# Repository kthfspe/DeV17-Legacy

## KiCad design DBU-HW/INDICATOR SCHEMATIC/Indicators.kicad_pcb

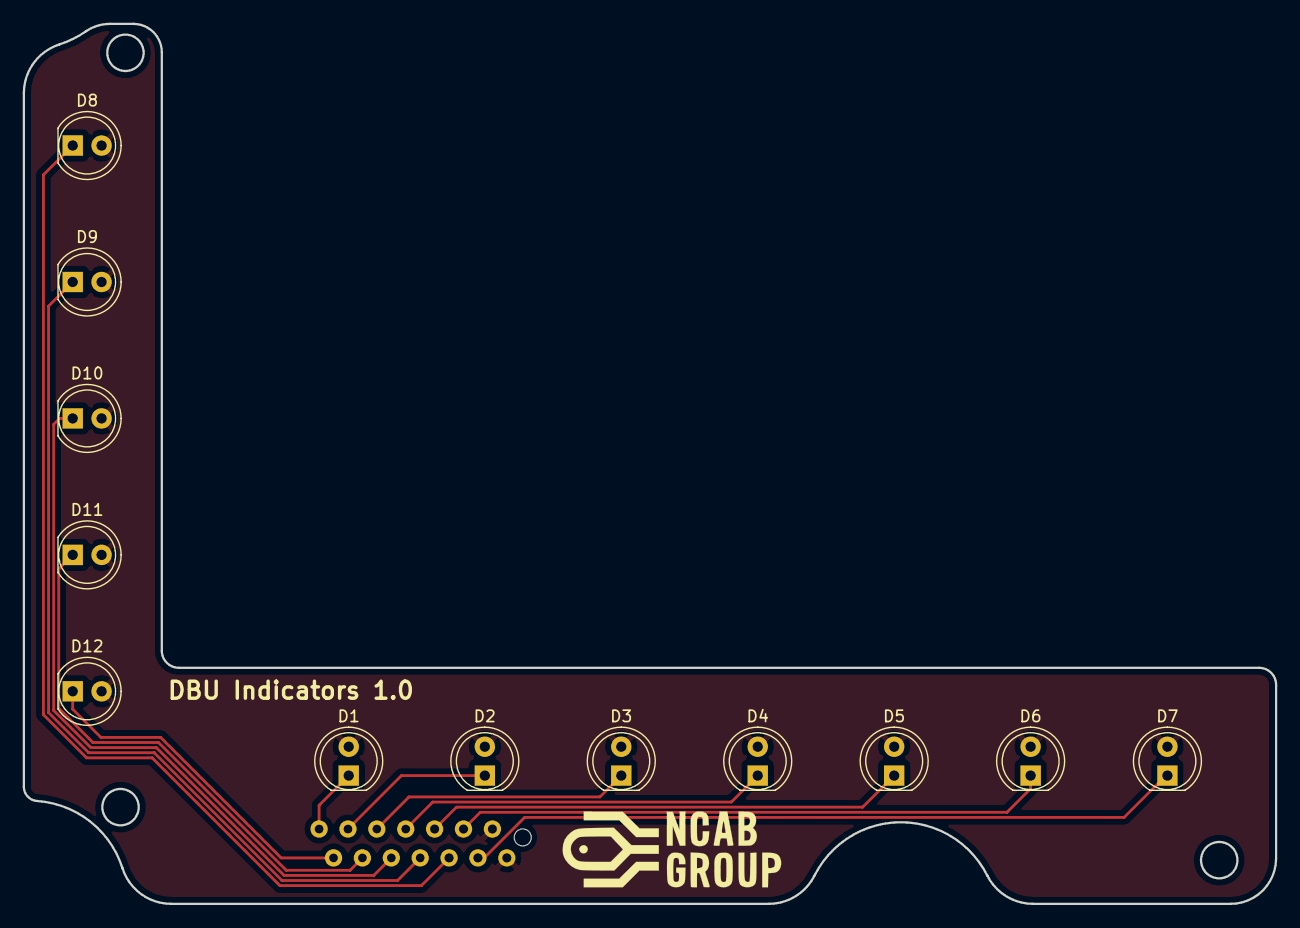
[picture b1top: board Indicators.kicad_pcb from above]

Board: 2 copper layers, 110.1 x 77.4 mm, 13 parts (1 on the bottom side), 13 nets.

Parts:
D1, D2, D3, D4, D5, D6, D7, D8, D9, D10, D11, D12: LED; LED_D5.0mm
J1: Conn_02x07_Odd_Even; Wurth-MM_female_14

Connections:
/AMI_1: D1.1, J1.14
/AMI_2: D2.1, J1.12
/AMI_3: D3.1, J1.10
/AMI_4: D4.1, J1.8
/AMI_5: D5.1, J1.6
/AMI_6: D6.1, J1.4
/AMI_7: D7.1, J1.3
/AMS_ERROR: D10.1, J1.9
/EBS_ERROR: D9.1, J1.7
/IMD_ERROR: D11.1, J1.11
/RESERVED: D12.1, J1.13
/TS_OFF: D8.1, J1.5
Vdrive: D1.2, D2.2, D3.2, D4.2, D5.2, D6.2, D7.2, D8.2, D9.2, D10.2, D11.2, D12.2, J1.1, J1.2

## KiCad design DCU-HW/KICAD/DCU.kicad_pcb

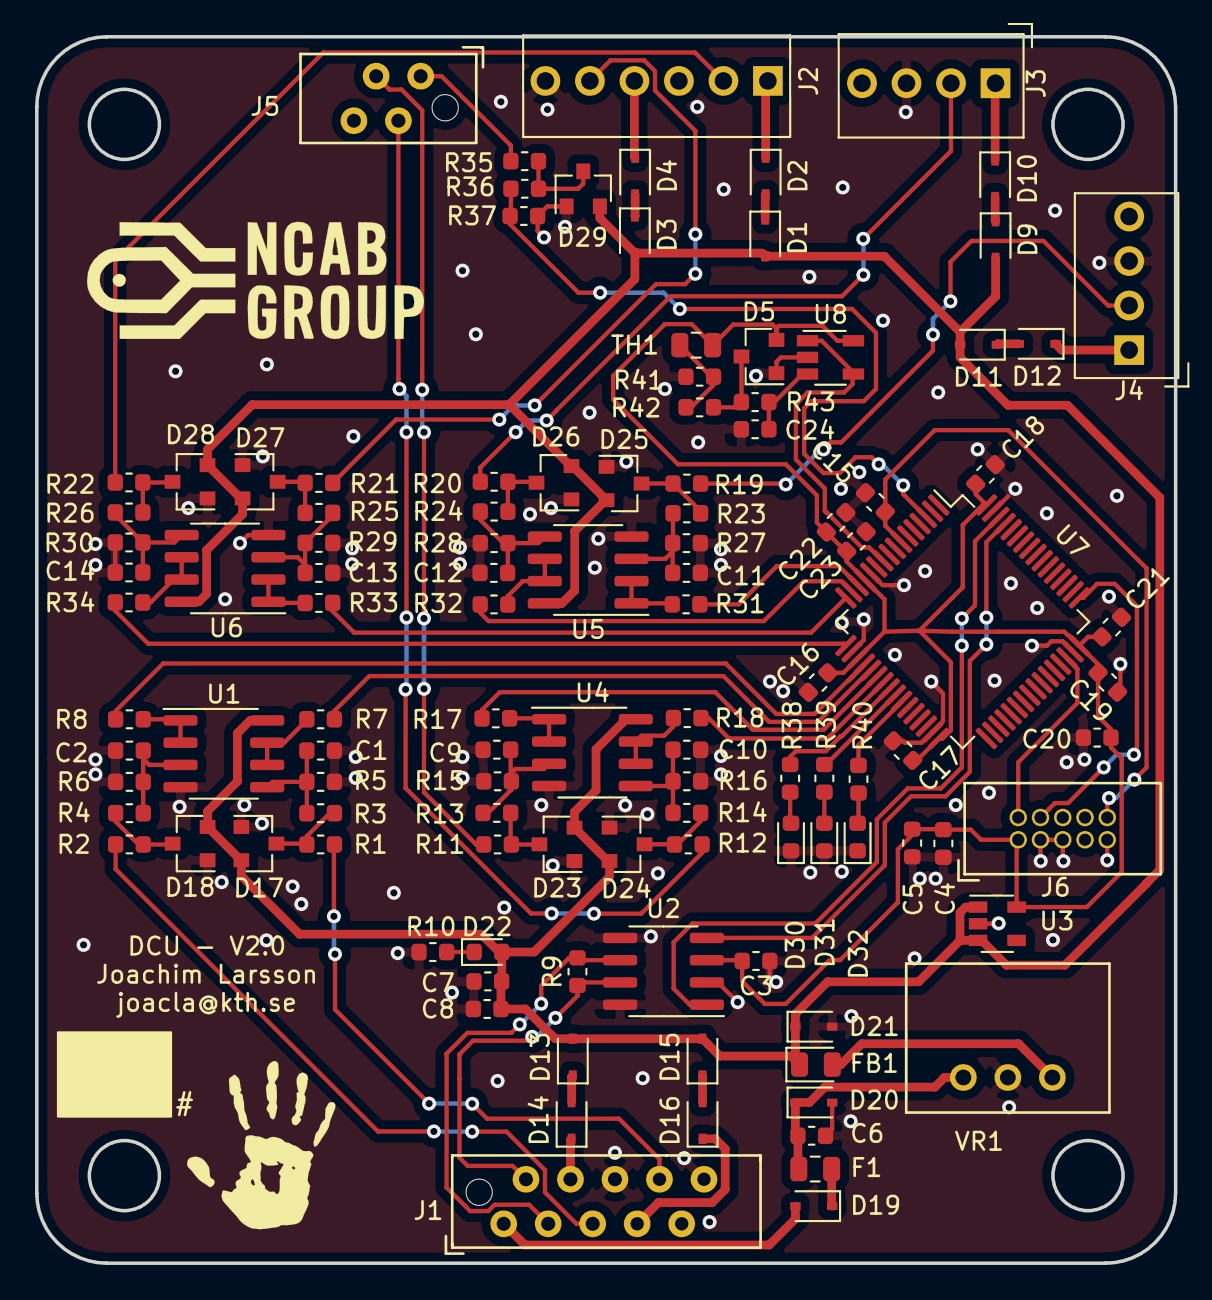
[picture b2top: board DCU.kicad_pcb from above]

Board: 2 copper layers, 65.0 x 70.0 mm, 114 parts (0 on the bottom side), 80 nets.

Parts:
C1, C2, C9, C10, C11, C12, C13, C14: 22n; C_0603_1608Metric
C3, C5, C8, C15, C16, C17, C18, C19, C24: 100n; C_0603_1608Metric
C4, C6, C7, C23: 1u; C_0603_1608Metric
C20, C21: 4.7u; C_0603_1608Metric
C22: 10n; C_0603_1608Metric
D1, D2, D3, D4, D9, D10, D11, D12, D13, D14, D15, D16: D; D_SOD-323
D5, D17, D18, D23, D24, D25, D26, D27, D28, D29: D_Schottky_x2_Serial_AKC; SOT-23
D19: SCHOTTKEY; D_SOD-323
D20, D21: TVS; D_SOD-323
D22: RED; LED_0603_1608Metric
D30: GREEN; LED_0603_1608Metric
D31: YELLOW; LED_0603_1608Metric
D32: BLUE; LED_0603_1608Metric
F1: Fuse; Fuse_0805_2012Metric
FB1: Ferrite_Bead; D_0805_2012Metric
J1: Conn_01x10_Female; Wurth-MM_female_10
J2: Conn_01x06_Female; Wurth-WTB_2.54_male_vert_6
J3: Conn_01x04_Male; Wurth-WTB_2.54_male_vert_4
J4: Conn_01x04_Female; Wurth-WTB_2.54_male_vert_4
J5: Conn_01x04_Female; Wurth-MM_female_4
J6: ARM_JTAG_SWD_10; Atmel_ICP_connector
R1, R2, R3, R4, R11, R12, R13, R14, R19, R20, R21, R22, R23, R24, R25, R26, R35: 200; R_0603_1608Metric
R5, R6, R10, R15, R16, R27, R28, R29, R30, R37: 510; R_0603_1608Metric
R7, R8, R17, R18, R31, R32, R33, R34, R42: 100; R_0603_1608Metric
R9: 120; R_0603_1608Metric
R36: 51; R_0603_1608Metric
R38, R39, R40, R43: 1k; R_0603_1608Metric
R41: 10k; R_0603_1608Metric
TH1: 10k; R_0805_2012Metric
U1, U4, U5, U6: LM358; SOIC-8_3.9x4.9mm_P1.27mm
U2: SN65HVD233; SOIC-8_3.9x4.9mm_P1.27mm
U3: ADP150AUJZ-3.3-R7; SOT-23-5
U7: STM32F091RCTx; LQFP-64_10x10mm_P0.5mm
U8: TLV9061; TSOT-23-5
VR1: Wurth-FDSM

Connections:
+3V3: C3.2, C4.1, C5.1, C16.1, C17.1, C18.1, C19.1, C20.1, C21.1, C22.1, C23.1, D5.2, J6.1, TH1.1, U2.3, U3.5, U7.13, U7.19, U7.32, U7.48, U7.64, U8.5
+5V: C7.1, C8.1, D1.2, D3.2, D9.2, D11.2, D13.2, D15.2, D17.2, D18.2, D21.1, D22.2, D23.2, D24.2, D25.2, D26.2, D27.2, D28.2, D29.2, FB1.1, U1.8, U3.1, U3.3, U4.8, U5.8, U6.8
+24V: C6.1, D20.1, F1.1, VR1.1
/APPS1_SIGNAL: J3.2, R20.2
/APPS1_SUPPLY: D10.1, J3.1
/APPS2_SIGNAL: J4.2, R19.2
/APPS2_SUPPLY: D12.1, J4.1
/BPPS1_SIGNAL: J2.2, R22.2
/BPPS1_SUPPLY: D2.1, J2.1
/BPPS2_SIGNAL: J2.5, R21.2
/BPPS2_SUPPLY: D4.1, J2.4
/BRAKE_PRESSURE_1_SIGNAL: J5.2, R12.2
/BRAKE_PRESSURE_2_SIGNAL: J5.3, R11.2
/BSPD_TRIGGERED_SIGNAL: J5.1, R35.2
/CAN1_H: J1.2, R9.1, U2.7
/CAN1_L: J1.3, R9.2, U2.6
/CONTROL_SYSTEMS_SUPPLY: D19.2, J1.1
/MCU/APPS1: R32.1, U7.15
/MCU/APPS2: R31.1, U7.14
/MCU/BPPS1: R34.1, U7.17
/MCU/BPPS2: R33.1, U7.16
/MCU/BRAKE_PRESSURE_1: R18.1, U7.23
/MCU/BRAKE_PRESSURE_2: R17.1, U7.22
/MCU/BSPD_TRIGGERED: R36.1, R37.2, U7.3
/MCU/CAN1_RX: U2.4, U7.61
/MCU/CAN1_TX: U2.1, U7.62
/MCU/JTAG_RESET_N: C15.1, J6.10, U7.7
/MCU/JTAG_SWDCLK: J6.4, U7.49
/MCU/JTAG_SWDIO: J6.2, U7.46
/MCU/MCU_STATUS_LED_1: R38.2, U7.24
/MCU/MCU_STATUS_LED_2: R39.2, U7.25
/MCU/MCU_STATUS_LED_3: R40.2, U7.26
/MCU/PCB_TEMPERATURE: U7.10, U8.1, U8.4
/MCU/STEERING_ANGLE_1: R8.1, U7.20
/MCU/STEERING_ANGLE_2: R7.1, U7.21
/STEERING_ANGLE_1_SIGNAL: J1.5, R2.2
/STEERING_ANGLE_1_SUPPLY: D14.1, J1.4
/STEERING_ANGLE_2_SIGNAL: J1.8, R1.2
/STEERING_ANGLE_2_SUPPLY: D16.1, J1.7
GND: C1.2, C2.2, C3.1, C4.2, C5.2, C6.2, C7.2, C8.2, C9.2, C10.2, C11.2, C12.2, C13.2, C14.2, C15.2, C16.2, C17.2, C18.2, C19.2, C20.2, C21.2, C22.2, C23.2, C24.2, D5.1, D17.1, D18.1, D20.2, D21.2, D23.1, D24.1, D25.1, D26.1, D27.1, D28.1, D29.1, D30.1, D31.1, D32.1, J1.6, J1.9, J1.10, J2.3, J2.6, J3.3, J4.3, J6.3, J6.5, J6.9, R5.2, R6.2, R10.2, R15.2, R16.2, R27.2, R28.2, R29.2, R30.2, R37.1, R41.1, U1.4, U2.2, U2.5, U2.8, U3.2, U4.4, U5.4, U6.4, U7.12, U7.18, U7.31, U7.47, U7.63, U8.2, VR1.2
unnamed: C1.1, R3.1, R5.1, U1.5
unnamed: C2.1, R4.1, R6.1, U1.3
unnamed: C9.1, R13.1, R15.1, U4.3
unnamed: C10.1, R14.1, R16.1, U4.5
unnamed: C11.1, R23.1, R27.1, U5.3
unnamed: C12.1, R24.1, R28.1, U5.5
unnamed: C13.1, R25.1, R29.1, U6.3
unnamed: C14.1, R26.1, R30.1, U6.5
unnamed: C24.1, R43.1, U8.3
unnamed: D1.1, D2.2
unnamed: D3.1, D4.2
unnamed: D5.3, R42.1, R43.2
unnamed: D9.1, D10.2
unnamed: D11.1, D12.2
unnamed: D13.1, D14.2
unnamed: D15.1, D16.2
unnamed: D17.3, R1.1, R3.2
unnamed: D18.3, R2.1, R4.2
unnamed: D19.1, F1.2
unnamed: D22.1, R10.1
unnamed: D23.3, R11.1, R13.2
unnamed: D24.3, R12.1, R14.2
unnamed: D25.3, R19.1, R23.2
unnamed: D26.3, R20.1, R24.2
unnamed: D27.3, R21.1, R25.2
unnamed: D28.3, R22.1, R26.2
unnamed: D29.3, R35.1, R36.2
unnamed: D30.2, R38.1
unnamed: D31.2, R39.1
unnamed: D32.2, R40.1
unnamed: FB1.2, VR1.3
unnamed: R7.2, U1.6, U1.7
unnamed: R8.2, U1.1, U1.2
unnamed: R17.2, U4.1, U4.2
unnamed: R18.2, U4.6, U4.7
unnamed: R31.2, U5.1, U5.2
unnamed: R32.2, U5.6, U5.7
unnamed: R33.2, U6.1, U6.2
unnamed: R34.2, U6.6, U6.7
unnamed: R41.2, R42.2, TH1.2
